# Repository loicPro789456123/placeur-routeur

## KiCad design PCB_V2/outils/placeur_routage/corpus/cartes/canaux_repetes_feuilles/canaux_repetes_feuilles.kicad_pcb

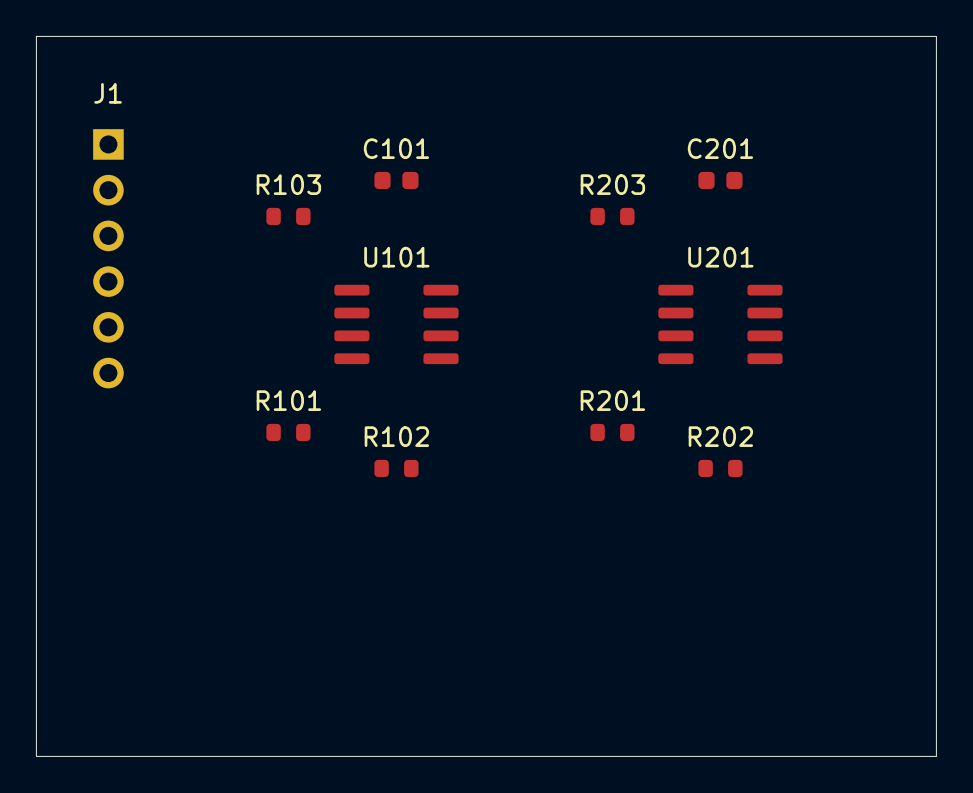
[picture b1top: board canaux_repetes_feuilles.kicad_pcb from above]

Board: 2 copper layers, 50.0 x 40.0 mm, 11 parts (0 on the bottom side), 10 nets, no tracks yet.

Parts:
C101, C201: 100n; C_0603_1608Metric
J1: Barrette; PinHeader_1x06_P2.54mm
R101, R103, R201, R203: 1k; R_0603_1608Metric
R102, R202: 10k; R_0603_1608Metric
U101, U201: Amplificateur; SOIC-8_3.9x4.9mm_P1.27mm

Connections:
+5V: C101.1, C201.1, J1.1, U101.8, U201.8
/canal1/IN: J1.3, R101.1
/canal1/INN: R102.1, R103.1, U101.2
/canal1/INP: R101.2, U101.3
/canal1/OUT: J1.4, R102.2, U101.1
/canal2/IN: J1.5, R201.1
/canal2/INN: R202.1, R203.1, U201.2
/canal2/INP: R201.2, U201.3
/canal2/OUT: J1.6, R202.2, U201.1
GND: C101.2, C201.2, J1.2, R103.2, R203.2, U101.4, U201.4

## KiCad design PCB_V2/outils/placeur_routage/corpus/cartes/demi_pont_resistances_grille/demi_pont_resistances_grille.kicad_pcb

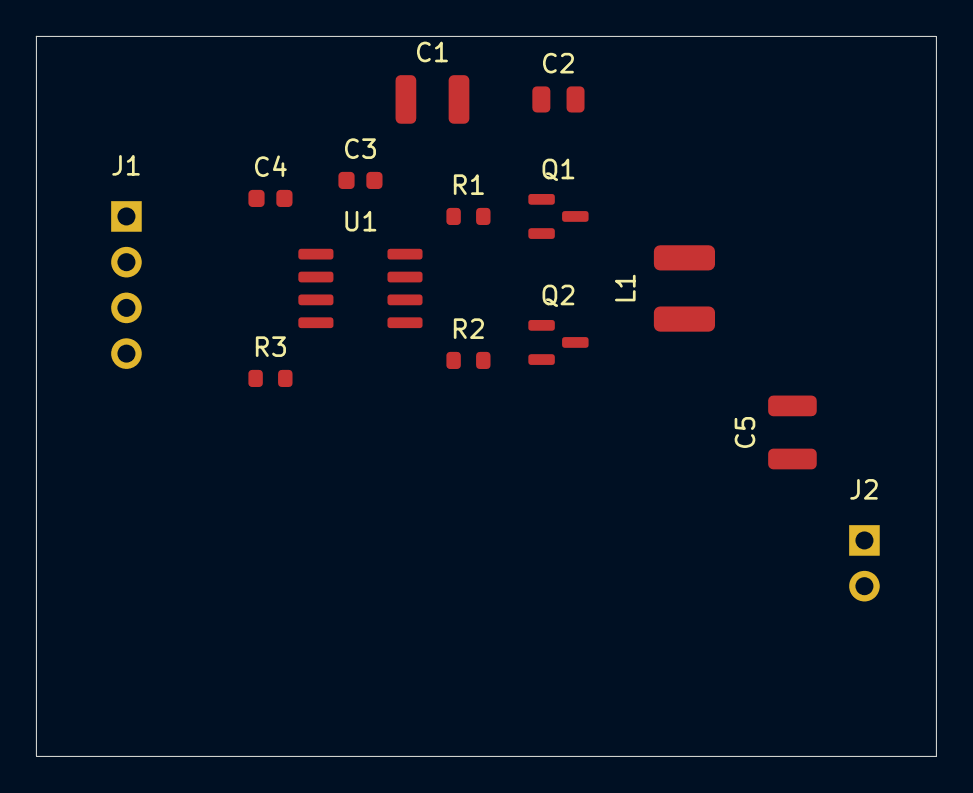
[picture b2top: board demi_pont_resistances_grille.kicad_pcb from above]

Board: 2 copper layers, 50.0 x 40.0 mm, 14 parts (0 on the bottom side), 12 nets, no tracks yet.

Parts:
C1, C5: 22u; C_1210_3225Metric
C2: 1u; C_0805_2012Metric
C3: 100n; C_0603_1608Metric
C4: 1u; C_0603_1608Metric
J1: Barrette; PinHeader_1x04_P2.54mm
J2: Barrette; PinHeader_1x02_P2.54mm
L1: 10uH; L_4x4
Q1, Q2: MOSFET N; SOT-23
R1: 4R7; R_0603_1608Metric
R2: 2R2; R_0603_1608Metric
R3: 100k; R_0603_1608Metric
U1: Pilote demi-pont; SOIC-8_3.9x4.9mm_P1.27mm

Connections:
+5V: C5.1, J2.1, L1.2
+12V: C1.1, C2.1, J1.1, Q1.3
EN: R3.2, U1.3
GH: Q1.1, R1.2
GH_U: R1.1, U1.7
GL: Q2.1, R2.2
GL_U: R2.1, U1.5
GND: C1.2, C2.2, C4.2, C5.2, J1.2, J2.2, Q2.2, U1.4
HB: C3.1, U1.8
PWM: J1.4, U1.2
SW: C3.2, L1.1, Q1.2, Q2.3, U1.6
VDRV: C4.1, J1.3, R3.1, U1.1

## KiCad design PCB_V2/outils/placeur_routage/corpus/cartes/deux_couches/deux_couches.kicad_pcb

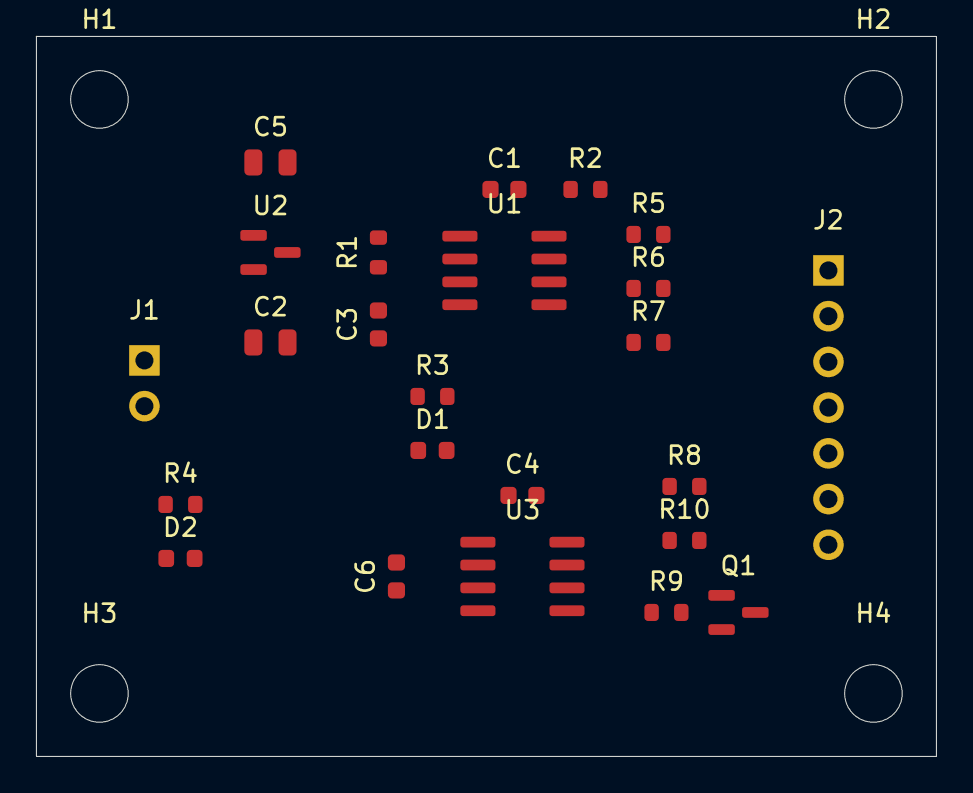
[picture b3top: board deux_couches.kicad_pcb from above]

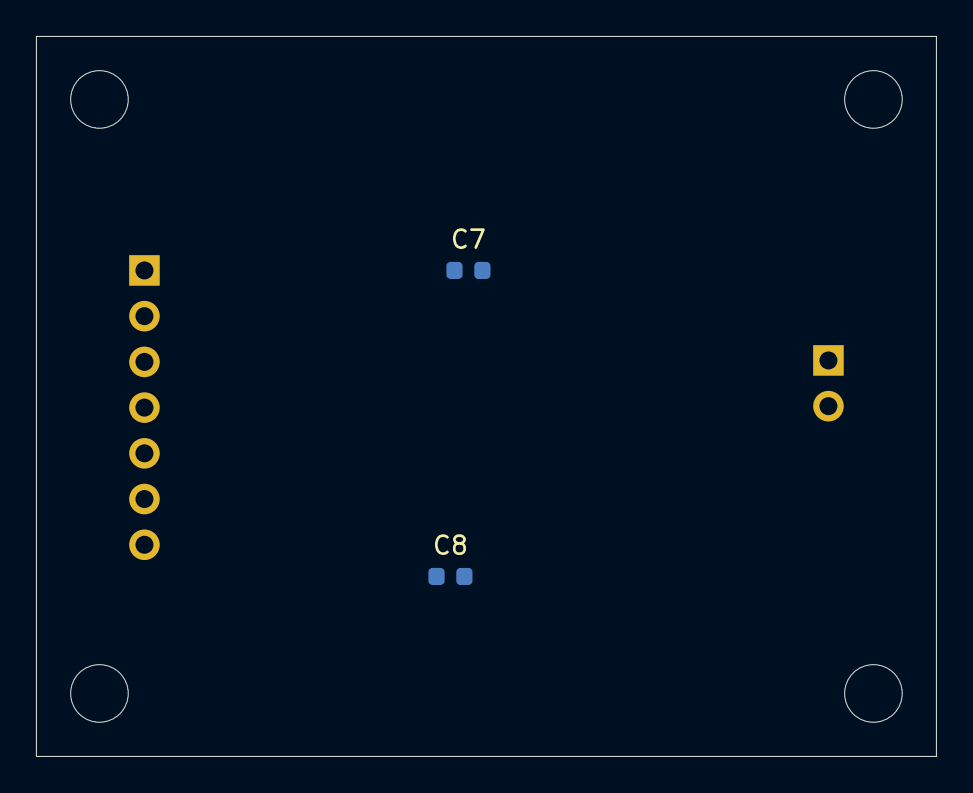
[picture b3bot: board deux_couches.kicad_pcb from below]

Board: 2 copper layers, 50.0 x 40.0 mm, 30 parts (2 on the bottom side), 21 nets, no tracks yet.

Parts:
C1, C3, C4, C7, C8: 100n; C_0603_1608Metric
C2, C5: 1u; C_0805_2012Metric
C6: 10n; C_0603_1608Metric
D1: Rouge; LED_0603_1608Metric
D2: Verte; LED_0603_1608Metric
H1, H2, H3, H4: Trou M3; MountingHole_3.2mm_M3
J1: Barrette; PinHeader_1x02_P2.54mm
J2: Barrette; PinHeader_1x07_P2.54mm
Q1: MOSFET N; SOT-23
R1: 10k; R_0603_1608Metric
R2: 4k7; R_0603_1608Metric
R3: 330; R_0603_1608Metric
R4, R8, R10: 1k; R_0603_1608Metric
R5, R6, R7: 33; R_0603_1608Metric
R9: 100; R_0603_1608Metric
U1: Microcontroleur; SOIC-8_3.9x4.9mm_P1.27mm
U2: Regulateur 3V3; SOT-23
U3: Comparateur; SOIC-8_3.9x4.9mm_P1.27mm

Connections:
+3V3: C1.1, C4.1, C5.1, C7.1, C8.1, R1.1, R2.1, U1.1, U2.2, U3.1, U3.7
+5V: C2.1, J1.1, R4.1, U2.3
D1_A: D1.2, R3.2
D2_A: D2.2, R4.2
GND: C1.2, C2.2, C3.2, C4.2, C5.2, C6.2, C7.2, C8.2, D1.1, D2.1, J1.2, Q1.2, U1.4, U2.1, U3.4, U3.8
IN_A: R8.2, U3.2
IN_J: J2.5, R8.1
LED1: R3.1, U1.3
LOAD: J2.7, Q1.3
OUT_B: R9.1, U3.3
Q_G: Q1.1, R9.2
RST: C3.1, R1.2, U1.2
RX: R7.1, U1.8
RX_J: J2.4, R7.2
SCL: R2.2, R5.1, U1.5
SCL_J: J2.1, R5.2
SDA: R6.1, U1.6
SDA_J: J2.2, R6.2
SENS: C6.1, R10.2, U3.6
SENS_J: J2.6, R10.1
TX: J2.3, U1.7

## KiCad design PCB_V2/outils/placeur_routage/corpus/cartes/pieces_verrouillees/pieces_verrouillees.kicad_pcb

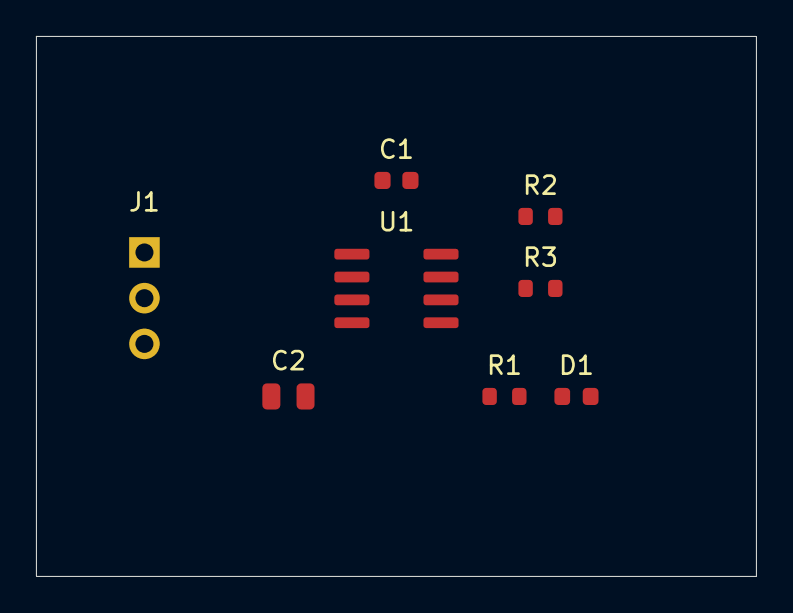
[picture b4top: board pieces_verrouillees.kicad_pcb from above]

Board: 2 copper layers, 40.0 x 30.0 mm, 8 parts (0 on the bottom side), 7 nets, no tracks yet.

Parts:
C1: 100n; C_0603_1608Metric
C2: 1u; C_0805_2012Metric
D1: Verte; LED_0603_1608Metric
J1: Barrette; PinHeader_1x03_P2.54mm
R1: 330; R_0603_1608Metric
R2, R3: 4k7; R_0603_1608Metric
U1: Microcontroleur; SOIC-8_3.9x4.9mm_P1.27mm

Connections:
+5V: C1.1, C2.1, J1.1, R2.1, R3.1, U1.1
GND: C1.2, C2.2, D1.1, J1.2, U1.4, U1.7, U1.8
IN: J1.3, U1.2
LED: R1.1, U1.3
LED_A: D1.2, R1.2
SCL: R2.2, U1.5
SDA: R3.2, U1.6

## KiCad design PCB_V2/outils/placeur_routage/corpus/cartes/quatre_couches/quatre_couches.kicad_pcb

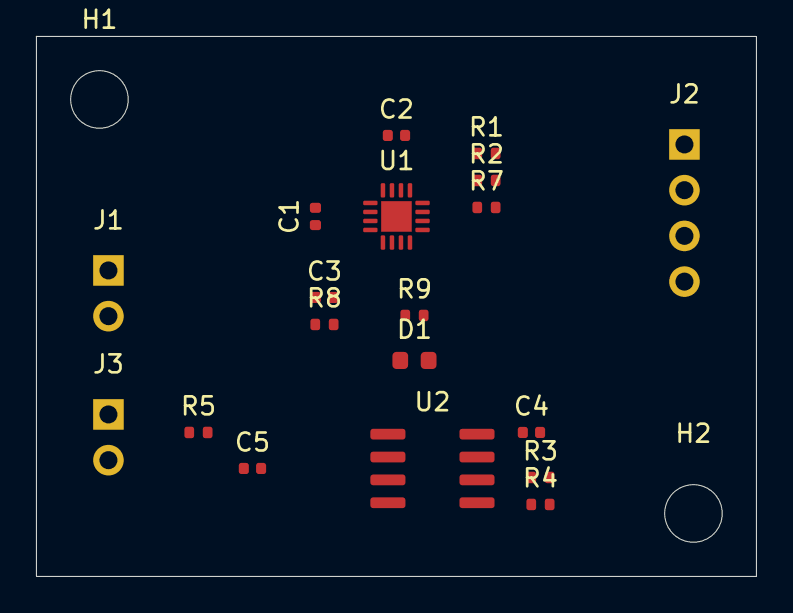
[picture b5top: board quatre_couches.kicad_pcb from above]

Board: 4 copper layers, 40.0 x 30.0 mm, 21 parts (0 on the bottom side), 12 nets, no tracks yet.

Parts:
C1, C2, C3, C4: 100n; C_0402_1005Metric
C5: 10n; C_0402_1005Metric
D1: Verte; LED_0603_1608Metric
H1, H2: Trou M3; MountingHole_3.2mm_M3
J1, J3: Barrette; PinHeader_1x02_P2.54mm
J2: Barrette; PinHeader_1x04_P2.54mm
R1, R2: 4k7; R_0402_1005Metric
R3: 22k; R_0402_1005Metric
R4, R8: 10k; R_0402_1005Metric
R5: 1k; R_0402_1005Metric
R7: 47k; R_0402_1005Metric
R9: 330; R_0402_1005Metric
U1: Microcontroleur; QFN-16_3x3mm_P0.5mm
U2: Amplificateur; SOIC-8_3.9x4.9mm_P1.27mm

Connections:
+3V3: C1.1, C2.1, C4.1, J1.1, R1.1, R2.1, R7.1, R8.1, U1.5, U1.11, U1.16, U2.8
FB_A: R3.1, R4.1, U2.2
GND: C1.2, C2.2, C3.2, C4.2, C5.2, D1.1, J1.2, J3.2, R4.2, U1.4, U1.7, U1.10, U1.15, U1.17, U2.4
INT: J2.3, R7.2, U1.3
LED: R9.1, U1.8
LED_A: D1.2, R9.2
RST: C3.1, R8.2, U1.6
SCL: J2.1, R1.2, U1.1
SDA: J2.2, R2.2, U1.2
SENS_IN: J3.1, R5.1
SENS_O: J2.4, R3.2, U2.1
SENS_P: C5.1, R5.2, U2.3

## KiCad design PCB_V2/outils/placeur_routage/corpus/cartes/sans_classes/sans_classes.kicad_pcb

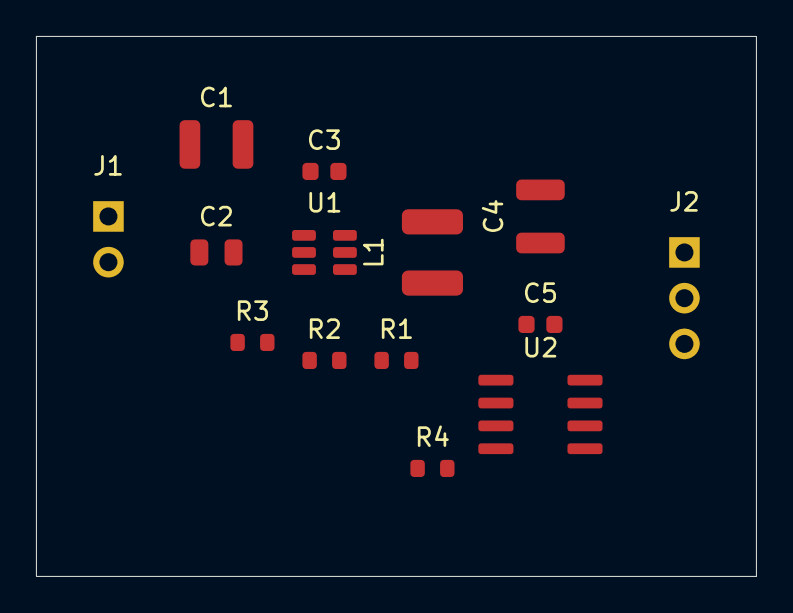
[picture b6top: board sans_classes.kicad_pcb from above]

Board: 2 copper layers, 40.0 x 30.0 mm, 14 parts (0 on the bottom side), 9 nets, no tracks yet.

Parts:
C1: 10u; C_1210_3225Metric
C2: 100n; C_0805_2012Metric
C3, C5: 100n; C_0603_1608Metric
C4: 22u; C_1210_3225Metric
J1: Barrette; PinHeader_1x02_P2.54mm
J2: Barrette; PinHeader_1x03_P2.54mm
L1: 10uH; L_4x4
R1: 52k3; R_0603_1608Metric
R2, R4: 10k; R_0603_1608Metric
R3: 100k; R_0603_1608Metric
U1: Abaisseur integre; SOT-23-6
U2: Charge logique; SOIC-8_3.9x4.9mm_P1.27mm

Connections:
+5V: C4.1, C5.1, J2.1, L1.2, R1.1, R4.1, U2.1
+12V: C1.1, C2.1, J1.1, R3.1, U1.5
BST: C3.1, U1.1
EN: R3.2, U1.4
FB: R1.2, R2.1, U1.3
GND: C1.2, C2.2, C4.2, C5.2, J1.2, J2.2, R2.2, U1.2, U2.4
IN: R4.2, U2.2
OUT: J2.3, U2.3
SW: C3.2, L1.1, U1.6
